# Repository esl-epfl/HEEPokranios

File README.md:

# HEEPokranios

HEEPokranios is a RISC-V SoC based on the open-source [X-HEEP](https://github.com/esl-epfl/x-heep) platform, designed to record intracranial EEG. Its 5 recording channels can be configured by the on-chip CPU and streamed out via DMA and different transmission options.

## SoC overview

- **MCU** — [X-HEEP](./hw/vendor/x-heep/): Ibex CPU, 2× DMA with dispatching mode, SPI (also used to load programs into SRAM wirelessly), JTAG, UART, 32 kB RAM, interrupts and timers.
- **Wireless power and data transfer** — [WPDT](./hw/vendor/analog-library/WPDT/): power from a 433 MHz inductive link, Manchester-encoded downlink (forwarded to the SPI) and uplink (serialized from a register), and a 1 MHz clock usable as system clock.
- **Power regulation** — [vREF](./hw/vendor/analog-library/vREF/), [iREF](./hw/vendor/analog-library/iREF/) and [iMIRROR](./hw/vendor/analog-library/iMIRROR/) generate the supplies and bias currents for the analog blocks from the WPDT rectifier output.
- **5× recording channels** — built as flavours of the [channel-multipath](./hw/ip/cheep_peripherals/peripherals/channel_multipath/) skeleton, combining acquisition blocks such as a low-noise amplifier ([LNA](./hw/vendor/analog-library/LNA/)), ΔΣ ADC ([DSM](./hw/vendor/analog-library/DSM/)), VCO-based ADC ([VCO](./hw/vendor/analog-library/VCO/)), level-crossing ADC ([LC](./hw/vendor/analog-library/LC/), [dLC](./hw/ip/cheep_peripherals/peripherals/dlc/)), band-power extraction ([BPE](./hw/vendor/analog-library/BPE/)) and an impedance-monitoring current DAC ([iDAC](./hw/vendor/analog-library/iDAC/)).

As a testing chip, most block inputs/outputs are exposed on pads, to be shorted at PCB level or at wire-bonding time.

## Getting started

1. Install the conda environment (Python tooling + fusesoc) and activate it:
   ```bash
   make conda
   conda activate heepokranios
   ```
   Make sure the following are also in your `PATH`: a RISC-V toolchain (supporting at least `rv32imc`), Verilator **4**, Verible and GTKWave. See _X-HEEP_'s [prerequisites](https://github.com/esl-epfl/x-heep#prerequisite) for details.

2. Generate the RTL and software from the SoC configuration (only needed once, and after any change to `config/cheep_configs.py` or a `.tpl` template):
   ```bash
   make mcu-gen
   ```

3. Build an application and run it on the Verilator simulation:
   ```bash
   make app PROJECT=hello_world
   make verilator-build
   make verilator-run
   ```
   The UART log is written to `build/sim-common/uart.log`, and waveforms can be inspected with `make verilator-waves`. `BOOT_MODE` defaults to `force` (firmware loaded directly into SRAM); `jtag` and `flash` boot are also supported.

`make help` lists all targets (use `make help WHICH=xheep` for the vendored _X-HEEP_ makefile).

## Documentation

- [_X-HEEP_ documentation](./hw/vendor/x-heep/docs/source/index.rst) — platform internals, configuration, programming and debugging.
- [HEEPokranios documentation](./docs/source/) — [analog front-end overview](./docs/source/Overview/Overview.md), [digital back-end](./docs/source/DBE/CIC_filter.md) and [LDO](./docs/source/FB/LDO.md) descriptions.
- [How to add new peripherals](./hw/ip/How%20to%20add%20new%20peripherals.md).
- [Analog library](./hw/vendor/analog-library/README.md) — structure and behavioral models of the analog blocks.

## License

HEEPokranios is distributed under the [Solderpad Hardware License v2.1](./LICENSE.md) (Apache-2.0 WITH SHL-2.1). The vendored [_X-HEEP_](./hw/vendor/x-heep/) and the analog library carry their own license terms.

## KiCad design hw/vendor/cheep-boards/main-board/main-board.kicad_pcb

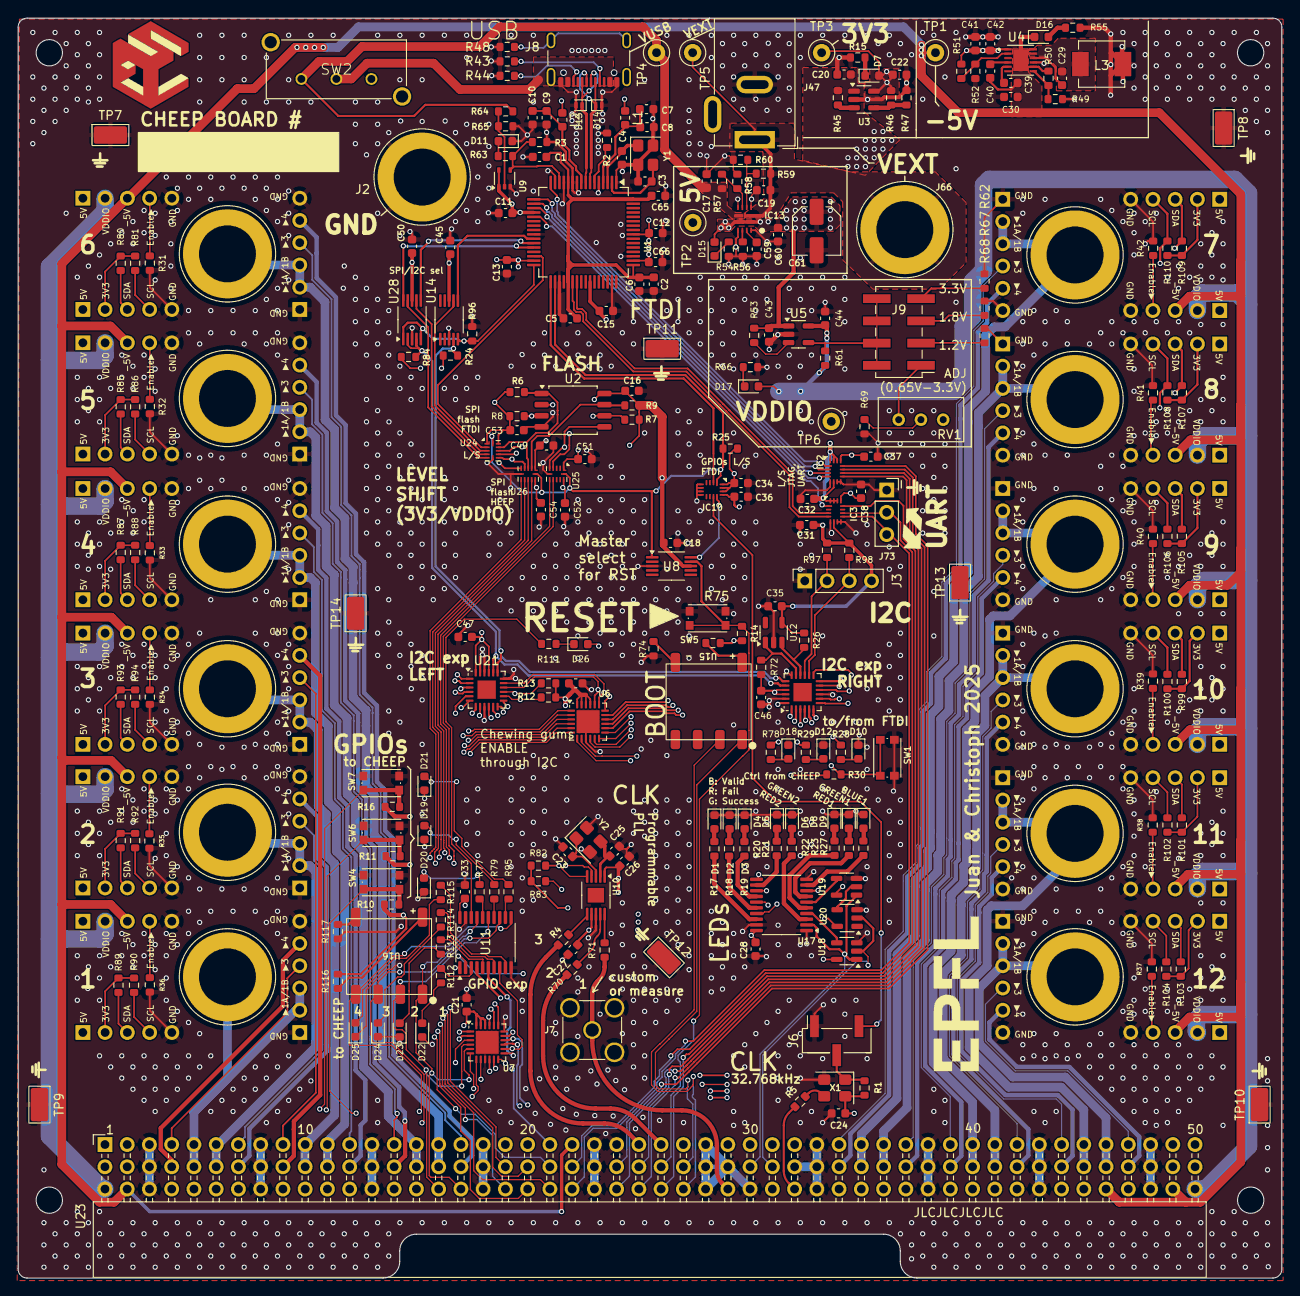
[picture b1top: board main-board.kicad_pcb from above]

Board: 4 copper layers, 144.3 x 143.8 mm, 277 parts (0 on the bottom side), 245 nets.

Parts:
C1, C2, C5, C7, C10, C11, C12, C13, C14, C15, C16, C18, C21, C24, C26, C27, C28, C29, C31, C32, C33, C34, C35, C36, C37, C38, C45, C46, C47, C49, C50, C51, C52, C53, C54, C59, C65, C66: 100nF; C_0603_1608Metric
C3, C4: 30pF; C_0603_1608Metric
C6: 3.3uF; C_0603_1608Metric
C8, C9, C41, C42: 4.7uF; C_0603_1608Metric
C17, C19, C60: 1uF; C_0603_1608Metric
C20, C43: 10uF; C_0603_1608Metric
C22, C30, C44: 22uF; C_0603_1608Metric
C23, C25: 1pF; C_0603_1608Metric
C39: 2.2uF; C_0603_1608Metric
C40: 5.6nF; C_0603_1608Metric
C61: 100uF; CP_Elec_5x4.5
CG1, CG2, CG3, CG4, CG5, CG6, CG7, CG8, CG9, CG10, CG11, CG12: chewing-gum
D1, D2, D3, D4, D5, D6, D7, D8, D9, D10, D11, D12, D15, D16, D17, D18, D19, D20, D21, D22, D23, D24, D25, D26: LED; LED_0603_1608Metric
D13, D14: PESD3V3U1UL; D_SOD-882
IC2, IC3, IC10: SN74AXC4T774RSVR; TI-UQFN-16
IC13: TPS2121RUXR; TI-VQFN-HR-12
J2, J66: Conn_01x01_Socket; Banana_Jack_1Pin
J3: Conn_01x04; PinSocket_1x04_P2.54mm_Vertical
J6: Conn_01x03; PinHeader_1x03_P2.54mm_Vertical_SMD_Pin1Right
J7: Conn_Boaxial; SMA_Amphenol_901-144_Vertical
J8: USB_C_Receptacle_USB2.0_16P; USB_C_Receptacle_GCT_USB4105-xx-A_16P_TopMnt_Horizontal
J9: Conn_02x04_Odd_Even; PinHeader_2x04_P2.54mm_Vertical_SMD
J47: Barrel Jack; BarrelJack_GCT_DCJ200-10-A_Horizontal
J73: Conn_01x03; PinSocket_1x03_P2.54mm_Vertical
L1, L2: 600nH; L_0603_1608Metric
L3: 10uH; L_Vishay_IHLP-2020
R1, R3, R12, R13, R24, R25, R26, R31, R32, R33, R34, R35, R36, R37, R38, R39, R40, R41, R42, R45, R53, R65, R72, R80, R81, R82, R83, R84, R85, R86, R87, R88, R89, R90, R91, R92, R93, R94, R96, R97, R98, R99, R100, R101, R102, R103, R104, R105, R106, R107, R108, R109, R110: 10k; R_0603_1608Metric
R2: 12k 1%; R_0603_1608Metric
R4, R5, R70, R71: 25; R_0603_1608Metric
R6, R7, R8, R9, R57, R59: 23.7k; R_0603_1608Metric
R10, R11, R14, R16, R30, R74, R75, R116, R117: 1k; R_0603_1608Metric
R15, R17, R18, R19, R20, R21, R22, R23, R27, R28, R29, R54, R55, R63, R66, R77, R78, R79, R95, R111, R112, R113, R114, R115: 5k; R_0603_1608Metric
R43, R44, R58, R60: 5.1k; R_0603_1608Metric
R46, R61: 100k; R_0603_1608Metric
R47, R62, R69: 20k; R_0603_1608Metric
R48: 51k; R_0603_1608Metric
R49: 226k; R_0603_1608Metric
R50: 49.9k; R_0603_1608Metric
R51: 3.32M; R_0603_1608Metric
R52: 1.33M; R_0603_1608Metric
R56: 59k; R_0603_1608Metric
R64: 4.7k; R_0603_1608Metric
R67: 44.2k; R_0603_1608Metric
R68: 86.6k; R_0603_1608Metric
RV1: 500k; Potentiometer_Bourns_3296W_Vertical
SW1, SW4, SW5, SW6, SW7: SW_Push; SW_Push_1P1T_NO_CK_KMR2
SW2: SW_DPST_x2; SW_TE_1825255-1
TP1, TP2, TP3, TP4, TP5, TP6: TestPoint_Loop_D1.80mm_Drill1.0mm_Beaded
TP7, TP8, TP9, TP10, TP11, TP12, TP13, TP14: 5029; TestPoint_Keystone_5019_Miniature
U1: FT4232HL; LQFP-64_10x10mm_P0.5mm
U2: W25Q128JVSIQ; SOIC-8_5.3x5.3mm_P1.27mm
U3, U5: TLV75801PDBV; SOT-23-5
U4: MAX17577; MAX17577-12-TDFN-EP
U6, U7: TCAL6416; WQFN-24-1EP_4x4mm_P0.5mm_EP2.6x2.6mm
U8, U14, U28: TS5A23159DGS; VSSOP-10_3x3mm_P0.5mm
U9: 74AHCT1G08; SOT-353_SC-70-5
U10: SI5351A-B-GTR; MSOP-10-1EP_3x3mm_P0.5mm_EP1.68x1.88mm
U11, U17: 74AHC244; TSSOP-20_4.4x6.5mm_P0.65mm
U12: 24AA02E-OT; SOT-23-5
U15, U16: BIWIN_DTS04GE_SMD
U18, U19: 74AHCT1G08; SOT-23-5
U20: 74AHC1G04; SOT-23-5
U21, U22: TCA9548ARGER; Texas_RGE0024C_VQFN-24-1EP_4x4mm_P0.5mm_EP2.1x2.1mm
U23: CHEEP_CONNECTOR_MAINBOARD
U24: TXBN0304RUT; Texas_R-PUQFN-N12
U25, U26: TXB0304RUT; Texas_R-PUQFN-N12
X1: OK322532.768KJBA4SL; Oscillator_SMD_SeikoEpson_SG8002CE-4Pin_3.2x2.5mm
Y1: Crystal_GND24; Crystal_SMD_3225-4Pin_3.2x2.5mm
Y2: NX3225GA-25.000M-STD-CRG-2; Crystal_SMD_3225-4Pin_3.2x2.5mm

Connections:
3V3: C11.1, C12.1, C13.1, C14.2, C15.1, C16.1, C18.1, C21.2, C22.1, C26.2, C28.2, C31.1, C32.1, C33.2, C34.1, C35.1, C45.1, C46.1, C47.1, C49.1, C50.1, C51.1, C53.1, C66.1, CG1.A2 (3V3), CG2.A2 (3V3), CG3.A2 (3V3), CG4.A2 (3V3), CG5.A2 (3V3), CG6.A2 (3V3), CG7.A2 (3V3), CG8.A2 (3V3), CG9.A2 (3V3), CG10.A2 (3V3), CG11.A2 (3V3), CG12.A2 (3V3), D7.2 (A), D26.2 (A), IC2.6 (DIR4), IC2.14 (VCCA), IC2.15 (DIR1), IC2.16 (DIR2), IC3.6 (DIR4), IC3.14 (VCCA), IC3.15 (DIR1), IC3.16 (DIR2), IC10.14 (VCCA), IC10.15 (DIR1), IC10.16 (DIR2), J3.4, L1.1, L2.1, R6.2, R7.2, R8.2, R9.2, R12.1, R13.1, R24.1, R25.1, R26.1, R30.2, R46.2, R72.1, R80.1, R81.1, R82.1, R83.1, R84.1, R85.1, R86.1, R87.1, R88.1, R89.1, R90.1, R91.1, R92.1, R93.1, R94.1, R97.1, R98.1, R99.1, R100.1, R101.1, R102.1, R103.1, R104.1, R105.1, R106.1, R107.1, R108.1, R109.1, R110.1, TP3.1, U1.20 (VCCIO), U1.31 (VCCIO), U1.42 (VCCIO), U1.50 (VREGIN), U1.56 (VCCIO), U2.8 (VCC), U3.5 (OUT), U6.18 (ADDR), U6.21 (VCCP), U6.22 (nINT), U6.23 (VCCI), U6.24 (nRST), U7.22 (nINT), U7.23 (VCCI), U7.24 (nRST), U8.8 (VCC), U9.1, U9.5 (VCC), U10.1 (VDD), U11.20 (VCC), U12.4 (V_{CC}), U14.8 (VCC), U17.20 (VCC), U18.5 (VCC), U19.5 (VCC), U20.5 (VCC), U21.21 (VCC), U21.24 (~RESET), U22.21 (VCC), U22.22 (A0), U22.24 (~RESET), U23.A2 (3V3), U23.A49 (3V3), U23.B2 (3V3), U23.B49 (3V3), U23.C44 (3V3), U24.1 (VCCA), U24.11 (VCCB), U25.1 (VCCA), U26.1 (VCCA), U28.8 (VCC)
5V: C20.1, C41.1, C42.1, C43.1, C60.1, C61.1, CG1.A1 (5V), CG1.B1 (5V), CG2.A1 (5V), CG2.B1 (5V), CG3.A1 (5V), CG3.B1 (5V), CG4.A1 (5V), CG4.B1 (5V), CG5.A1 (5V), CG5.B1 (5V), CG6.A1 (5V), CG6.B1 (5V), CG7.A1 (5V), CG7.B1 (5V), CG8.A1 (5V), CG8.B1 (5V), CG9.A1 (5V), CG9.B1 (5V), CG10.A1 (5V), CG10.B1 (5V), CG11.A1 (5V), CG11.B1 (5V), CG12.A1 (5V), CG12.B1 (5V), D15.2 (A), IC13.1 (VOUT_1), IC13.8 (VOUT_2), R45.2, R51.1, R53.2, TP2.1, U3.1 (IN), U4.1 (IN), U5.1 (IN), U23.A1 (5V), U23.A50 (5V), U23.B1 (5V), U23.B50 (5V), U23.C45 (5V)
-5V: C30.2, C39.2, C40.2, CG1.B3 (-5V), CG2.B3 (-5V), CG3.B3 (-5V), CG4.B3 (-5V), CG5.B3 (-5V), CG6.B3 (-5V), CG7.B3 (-5V), CG8.B3 (-5V), CG9.B3 (-5V), CG10.B3 (-5V), CG11.B3 (-5V), CG12.B3 (-5V), D16.1 (K), R50.2, TP1.1, U4.8 (SOUT), U4.12 (OUT), U4.13 (EP), U23.A22 (-5V), U23.C2 (-5V), U23.C46 (-5V), U23.C49 (-5V)
/BOOT_SEL: U15.1, U23.B27 (BOOT_SEL)
/BTN_FTDI: R30.1, SW1.1, U6.14
/CG_I2C_SCL_1: CG1.A4 (SCL), R90.2, U21.6 (SC2)
/CG_I2C_SCL_2: CG2.A4 (SCL), R92.2, U21.4 (SC1)
/CG_I2C_SCL_3: CG3.A4 (SCL), R94.2, U21.2 (SC0)
/CG_I2C_SCL_4: CG4.A4 (SCL), R88.2, U21.8 (SC3)
/CG_I2C_SCL_5: CG5.A4 (SCL), R86.2, U21.11 (SC4)
/CG_I2C_SCL_6: CG6.A4 (SCL), R81.2, U21.13 (SC5)
/CG_I2C_SCL_7: CG7.A4 (SCL), R110.2, U22.2 (SC0)
/CG_I2C_SCL_8: CG8.A4 (SCL), R108.2, U22.4 (SC1)
/CG_I2C_SCL_9: CG9.A4 (SCL), R106.2, U22.6 (SC2)
/CG_I2C_SCL_10: CG10.A4 (SCL), R100.2, U22.13 (SC5)
/CG_I2C_SCL_11: CG11.A4 (SCL), R102.2, U22.11 (SC4)
/CG_I2C_SCL_12: CG12.A4 (SCL), R104.2, U22.8 (SC3)
/CG_I2C_SDA_1: CG1.A3 (SDA), R89.2, U21.5 (SD2)
/CG_I2C_SDA_2: CG2.A3 (SDA), R91.2, U21.3 (SD1)
/CG_I2C_SDA_3: CG3.A3 (SDA), R93.2, U21.1 (SD0)
/CG_I2C_SDA_4: CG4.A3 (SDA), R87.2, U21.7 (SD3)
/CG_I2C_SDA_5: CG5.A3 (SDA), R85.2, U21.10 (SD4)
/CG_I2C_SDA_6: CG6.A3 (SDA), R80.2, U21.12 (SD5)
/CG_I2C_SDA_7: CG7.A3 (SDA), R109.2, U22.1 (SD0)
/CG_I2C_SDA_8: CG8.A3 (SDA), R107.2, U22.3 (SD1)
/CG_I2C_SDA_9: CG9.A3 (SDA), R105.2, U22.5 (SD2)
/CG_I2C_SDA_10: CG10.A3 (SDA), R99.2, U22.12 (SD5)
/CG_I2C_SDA_11: CG11.A3 (SDA), R101.2, U22.10 (SD4)
/CG_I2C_SDA_12: CG12.A3 (SDA), R103.2, U22.7 (SD3)
/CHEEP-CONNECTOR/CHEEP_I2C.SCL: R13.2, U21.15 (SC6), U23.C4 (I2C_SDA)
/CHEEP-CONNECTOR/CHEEP_I2C.SDA: R12.2, U21.14 (SD6), U23.C5 (I2C_SCL)
/CHEEP-CONNECTOR/JTAG.TCK: IC2.12 (B1), U23.B24 (JTAG_TCK)
/CHEEP-CONNECTOR/JTAG.TDI: IC2.11 (B2), U23.C25 (JTAG_TDI)
/CHEEP-CONNECTOR/JTAG.TDO: IC2.10 (B3), U23.C24 (JTAG_TDO)
/CHEEP-CONNECTOR/JTAG.TMS: IC2.9 (B4), U23.B25 (JTAG_TMS)
/CHEEP-CONNECTOR/JTAG.TRST: IC3.12 (B1), U23.C26 (JTAG_TRST)
/CHEEP-CONNECTOR/SPI_FLASH.CS0: U23.C19 (SPI_FLASH_SCK), U26.9 (B2)
/CHEEP-CONNECTOR/SPI_FLASH.SCK: U23.B19 (SPI_FLASH_CS), U25.8 (B3)
/CHEEP-CONNECTOR/SPI_FLASH.SD0: U23.B20 (SPI_FLASH_SD0), U25.7 (B4)
/CHEEP-CONNECTOR/SPI_FLASH.SD1: U23.C20 (SPI_FLASH_SD1), U26.8 (B3)
/CHEEP-CONNECTOR/SPI_FLASH.SD2: U23.B21 (SPI_FLASH_SD2), U26.7 (B4)
/CHEEP-CONNECTOR/SPI_FLASH.SD3: U23.C21 (SPI_FLASH_SD3), U26.10 (B1)
/CHEEP-CONNECTOR/UART.RX: IC3.10 (B3), J73.2, U23.B22 (UART_RX)
/CHEEP-CONNECTOR/UART.TX: IC3.9 (B4), J73.3, U23.C22 (UART_TX)
/CLK2: R70.1, U23.A26 (CLK2)
/CLK3: R4.1, U23.A25 (CLK3)
/CLK32K: R5.2, U23.C32 (CLK_32khz)
/CLOCK: J7.1 (In), R71.1, U23.C29 (CLK_FAST)
/CLOCK_SEL: IC10.11 (B2), J6.3
/EN_CG_1: CG1.B4 (ENABLE), R36.1, U6.6 (P05)
/EN_CG_2: CG2.B4 (ENABLE), R35.1, U6.5 (P04)
/EN_CG_3: CG3.B4 (ENABLE), R34.1, U6.4 (P03)
/EN_CG_4: CG4.B4 (ENABLE), R33.1, U6.3 (P02)
/EN_CG_5: CG5.B4 (ENABLE), R32.1, U6.2 (P01)
/EN_CG_6: CG6.B4 (ENABLE), R31.1, U6.1 (P00)
/EN_CG_7: CG7.B4 (ENABLE), R42.1, U6.13
/EN_CG_8: CG8.B4 (ENABLE), R41.1, U6.12
/EN_CG_9: CG9.B4 (ENABLE), R40.1, U6.11
/EN_CG_10: CG10.B4 (ENABLE), R39.1, U6.10
/EN_CG_11: CG11.B4 (ENABLE), R38.1, U6.8 (P07)
/EN_CG_12: CG12.B4 (ENABLE), R37.1, U6.7 (P06)
/EP_CLOCK_SEL: IC10.2 (A2), U1.33 (BDBUS6)
/EP_F_CS: U1.30 (BDBUS4), U24.2 (A1)
/EP_F_MISO: U24.5 (A4), U28.9
/EP_F_MOSI: U24.4 (A3), U28.7
/EP_F_SCK: U14.7, U24.3 (A2)
/EP_RX0: IC3.3 (A3), U1.39 (CDBUS1)
/EP_TCK: IC2.1 (A1), U1.16 (ADBUS0)
/EP_TDI: IC2.2 (A2), U1.17 (ADBUS1)
/EP_TDO: IC2.3 (A3), U1.18 (ADBUS2)
/EP_TMS: IC2.4 (A4), U1.19 (ADBUS3)
/EP_TRST: IC3.1 (A1), U1.21 (ADBUS4)
/EP_TX0: IC3.4 (A4), U1.38 (CDBUS0)
/EXEC_FLASH: U15.2, U23.C27 (EXEC_FLASH)
/EXIT_VALID: U17.2 (1A0), U18.1, U19.1, U23.B30 (EXIT_VALID)
/EXIT_VALUE: U18.2, U20.2, U23.B31 (EXIT_VALUE)
/GPIO_15: U7.3 (P02), U23.C9 (GPIO_15)
/GPIO_16: U7.2 (P01), U23.A32 (GPIO_16)
/GPIO_17: U7.1 (P00), U23.A31 (GPIO_17)
/GPIO_18: U7.15, U23.A30 (GPIO_18)
/GPIO_19: U7.16, U23.A29 (GPIO_19)
/GPIO_20: U7.17, U23.A21 (GPIO_20)
/GPIO_playground/GPIO.LED_B_1: U17.11 (2A3), U23.C39 (GPIO_3)
/GPIO_playground/GPIO.LED_G_1: U7.6 (P05), U17.13 (2A2), U23.C34 (GPIO_7)
/GPIO_playground/GPIO.LED_G_2: U7.8 (P07), U17.17 (2A0), U23.C36 (GPIO_5)
/GPIO_playground/GPIO.LED_R_1: U7.7 (P06), U17.15 (2A1), U23.C35 (GPIO_6)
/GPIO_playground/GPIO.LED_R_2: U17.8 (1A3), U23.C37 (GPIO_4)
/GPIO_playground/GPIO.PB_1: R10.1, SW4.1, U7.12, U11.4 (1A1), U23.C12 (GPIO_12)
/GPIO_playground/GPIO.PB_2: R11.1, SW6.1, U7.13, U11.6 (1A2), U23.C11 (GPIO_13)
/GPIO_playground/GPIO.PB_3: R16.1, SW7.1, U7.14, U11.8 (1A3), U23.C10 (GPIO_14)
/GPIO_playground/GPIO.SW_1: U7.5 (P04), U11.17 (2A0), U16.1, U23.C17 (GPIO_8)
/GPIO_playground/GPIO.SW_2: U7.4 (P03), U11.15 (2A1), U16.2, U23.C16 (GPIO_9)
/GPIO_playground/GPIO.SW_3: U7.10, U11.13 (2A2), U16.3, U23.C15 (GPIO_10)
/GPIO_playground/GPIO.SW_4: U7.11, U11.11 (2A3), U16.4, U23.C14 (GPIO_11)
/I2C_expander/SCL_EEPROM: R72.2, U12.1 (SCL), U22.17 (SC7)
/I2C_expander/SCL_EXT: J3.2, R97.2, U22.15 (SC6)
/I2C_expander/SDA_EEPROM: R26.2, U12.3 (SDA), U22.16 (SD7)
/I2C_expander/SDA_EXT: J3.3, R98.2, U22.14 (SD6)
/LED_FTDI_1: R28.1, U6.17
/LED_FTDI_2: R29.1, U6.16
/LED_FTDI_3: R78.1, U6.15
/LX: C29.2, L3.1, U4.11 (LX)
/LevelTransMeasCurrent/FLASH_CS: R6.1, U2.1 (~CS), U24.10 (B1), U26.3 (A2)
/LevelTransMeasCurrent/FLASH_MISO: U2.2 (DO/IO1), U24.7 (B4), U26.4 (A3)
/LevelTransMeasCurrent/FLASH_MOSI: U2.5 (DI/IO0), U24.8 (B3), U25.5 (A4)
/LevelTransMeasCurrent/FLASH_SCK: R7.1, U2.6 (CLK), U24.9 (B2), U25.4 (A3)
/LevelTransMeasCurrent/FLASH_nHLD_nRST: R9.1, U2.7 (~HLD/~RST/IO3), U26.2 (A1)
/LevelTransMeasCurrent/FLASH_nWP: R8.1, U2.3 (~WP/IO2), U26.5 (A4)
/Programmer/FLASH_MISO_SDA: U1.28 (BDBUS2), U28.10
/Programmer/FLASH_MOSI_SDA: U1.27 (BDBUS1), U28.6
/Programmer/FLASH_SCK_SCL: U1.26 (BDBUS0), U14.6
/Programmer/FTDI_ACTIVE: R3.1, R63.2, U1.14 (~RESET), U9.4
/Programmer/SPI_I2C_SEL: R96.1, U1.32 (BDBUS5), U14.5, U28.1, U28.5
/Programmer/VCORE: C1.1, C2.1, C5.1, C6.1, C65.1, U1.12 (VCORE), U1.37 (VCORE), U1.49 (VREGOUT), U1.64 (VCORE)
/USB_D+: D13.1 (K), J8.A6 (D+), J8.B6 (D+), U1.8 (DP)
/USB_D-: D14.1 (K), J8.A7 (D-), J8.B7 (D-), U1.7 (DM)
/VBUS: J8.A4 (VBUS), J8.A9 (VBUS), J8.B4 (VBUS), J8.B9 (VBUS), SW2.2 (B)
/VEXT: C19.2, IC13.2 (VIN2), J47.1, J66.1, R59.1, TP5.1
/VUSB: C17.1, IC13.7 (VIN1), R57.2, R64.1, SW2.1 (A), TP4.1
/Vout_A_1: CG1.C2 (OUT_1), CG1.C3 (OUT_2), CG1.D1 (OUT_0), U23.A5 (VOUT.A1.1), U23.B5 (VOUT.A1.1)
/Vout_A_2: CG2.C2 (OUT_1), CG2.C3 (OUT_2), CG2.D1 (OUT_0), U23.A6 (VOUT.A2.1), U23.B6 (VOUT.A2.1)
/Vout_A_3: CG3.C2 (OUT_1), CG3.C3 (OUT_2), CG3.D1 (OUT_0), U23.A10 (VOUT.A3.1), U23.B10 (VOUT.A3.1)
/Vout_A_4: CG4.C2 (OUT_1), CG4.C3 (OUT_2), CG4.D1 (OUT_0), U23.A11 (VOUT.A4.1), U23.B11 (VOUT.A4.1)
/Vout_A_5: CG5.C2 (OUT_1), CG5.C3 (OUT_2), CG5.D1 (OUT_0), U23.A15 (VOUT.A5.1), U23.B15 (VOUT.A5.1)
/Vout_A_6: CG6.C2 (OUT_1), CG6.C3 (OUT_2), CG6.D1 (OUT_0), U23.A16 (VOUT.A6.1), U23.B16 (VOUT.A6.1)
/Vout_A_7: CG7.C2 (OUT_1), CG7.C3 (OUT_2), CG7.D1 (OUT_0), U23.A35 (VOUT.A7.1), U23.B35 (VOUT.A7.1)
/Vout_A_8: CG8.C2 (OUT_1), CG8.C3 (OUT_2), CG8.D1 (OUT_0), U23.A36 (VOUT.A8.1), U23.B36 (VOUT.A8.1)
/Vout_A_9: CG9.C2 (OUT_1), CG9.C3 (OUT_2), CG9.D1 (OUT_0), U23.A40 (VOUT.A9.1), U23.B40 (VOUT.A9.1)
/Vout_A_10: CG10.C2 (OUT_1), CG10.C3 (OUT_2), CG10.D1 (OUT_0), U23.A41 (VOUT.A10.1), U23.B41 (VOUT.A10.1)
/Vout_A_11: CG11.C2 (OUT_1), CG11.C3 (OUT_2), CG11.D1 (OUT_0), U23.A45 (VOUT.A11.1), U23.B45 (VOUT.A11.1)
/Vout_A_12: CG12.C2 (OUT_1), CG12.C3 (OUT_2), CG12.D1 (OUT_0), U23.A46 (VOUT.A12.1), U23.B46 (VOUT.A12.1)
/Vout_B_1: CG1.C5 (OUT_4), U23.B4 (VOUT.B1.1)
/Vout_B_2: CG2.C5 (OUT_4), U23.B7 (VOUT.B2.1)
/Vout_B_3: CG3.C5 (OUT_4), U23.B9 (VOUT.B3.1)
/Vout_B_4: CG4.C5 (OUT_4), U23.B12 (VOUT.B4.1)
/Vout_B_5: CG5.C5 (OUT_4), U23.B14 (VOUT.B5.1)
/Vout_B_6: CG6.C5 (OUT_4), U23.B17 (VOUT.B6.1)
/Vout_B_7: CG7.C5 (OUT_4), U23.B34 (VOUT.B7.1)
/Vout_B_8: CG8.C5 (OUT_4), U23.B37 (VOUT.B8.1)
/Vout_B_9: CG9.C5 (OUT_4), U23.B39 (VOUT.B9.1)
/Vout_B_10: CG10.C5 (OUT_4), U23.B42 (VOUT.B10.1)
/Vout_B_11: CG11.C5 (OUT_4), U23.B44 (VOUT.B11.1)
/Vout_B_12: CG12.C5 (OUT_4), U23.B47 (VOUT.B12.1)
/Vout_diff_1: CG1.C4 (OUT_3), U23.A4 (VOUT.B1.diff)
/Vout_diff_2: CG2.C4 (OUT_3), U23.A7 (VOUT.B2.diff)
/Vout_diff_3: CG3.C4 (OUT_3), U23.A9 (VOUT.B3.diff)
/Vout_diff_4: CG4.C4 (OUT_3), U23.A12 (VOUT.B4.diff)
/Vout_diff_5: CG5.C4 (OUT_3), U23.A14 (VOUT.B5.diff)
/Vout_diff_6: CG6.C4 (OUT_3), U23.A17 (VOUT.B6.diff)
/Vout_diff_7: CG7.C4 (OUT_3), U23.A34 (VOUT.B7.diff)
/Vout_diff_8: CG8.C4 (OUT_3), U23.A37 (VOUT.B8.diff)
/Vout_diff_9: CG9.C4 (OUT_3), U23.A39 (VOUT.B9.diff)
/Vout_diff_10: CG10.C4 (OUT_3), U23.A42 (VOUT.B10.diff)
/Vout_diff_11: CG11.C4 (OUT_3), U23.A44 (VOUT.B11.diff)
/Vout_diff_12: CG12.C4 (OUT_3), U23.A47 (VOUT.B12.diff)
/nRST: R14.1, SW5.1, U8.9, U11.2 (1A0), U23.B26 (nRST)
/nRST_HEEP_FTDI: IC10.1 (A1), R25.2, U1.34 (BDBUS7), U8.1, U24.12 (~OE), U25.12 (OE), U26.12 (OE)
GND: C1.2, C2.2, C3.1, C4.1, C5.2, C6.2, C7.2, C8.2, C9.2, C10.2, C11.2, C12.2, C13.2, C14.1, C15.2, C16.2, C17.2, C18.2, C19.1, C20.2, C21.1, C22.2, C23.2, C24.2, C25.2, C26.1, C27.2, C28.1, C30.1, C31.2, C32.2, C33.1, C34.2, C35.2, C36.2, C37.2, C38.2, C41.2, C42.2, C43.2, C44.2, C45.2, C46.2, C47.2, C49.2, C50.2, C51.2, C52.2, C53.2, C54.2, C59.2, C60.2, C61.2, C65.2, C66.2, CG1.A5 (GND), CG1.B5 (GND), CG1.C1 (GND), CG1.C6 (GND), CG2.A5 (GND), CG2.B5 (GND), CG2.C1 (GND), CG2.C6 (GND), CG3.A5 (GND), CG3.B5 (GND), CG3.C1 (GND), CG3.C6 (GND), CG4.A5 (GND), CG4.B5 (GND), CG4.C1 (GND), CG4.C6 (GND), CG5.A5 (GND), CG5.B5 (GND), CG5.C1 (GND), CG5.C6 (GND), CG6.A5 (GND), CG6.B5 (GND), CG6.C1 (GND), CG6.C6 (GND), CG7.A5 (GND), CG7.B5 (GND), CG7.C1 (GND), CG7.C6 (GND), CG8.A5 (GND), CG8.B5 (GND), CG8.C1 (GND), CG8.C6 (GND), CG9.A5 (GND), CG9.B5 (GND), CG9.C1 (GND), CG9.C6 (GND), CG10.A5 (GND), CG10.B5 (GND), CG10.C1 (GND), CG10.C6 (GND), CG11.A5 (GND), CG11.B5 (GND), CG11.C1 (GND), CG11.C6 (GND), CG12.A5 (GND), CG12.B5 (GND), CG12.C1 (GND), CG12.C6 (GND), D1.1 (K), D2.1 (K), D3.1 (K), D4.1 (K), D5.1 (K), D6.1 (K), D8.1 (K), D9.1 (K), D10.1 (K), D11.1 (K), D12.1 (K), D13.2 (A), D14.2 (A), D18.1 (K), D19.1 (K), D20.1 (K), D21.1 (K), D22.1 (K), D23.1 (K), D24.1 (K), D25.1 (K), IC2.5 (DIR3), IC2.7 (~OE), IC2.8 (GND), IC3.5 (DIR3), IC3.7 (~OE), IC3.8 (GND), IC10.5 (DIR3), IC10.6 (DIR4), IC10.7 (~OE), IC10.8 (GND), IC13.3 (CP2), IC13.6 (PR1), IC13.9 (ST), IC13.12 (GND), J2.1, J3.1, J6.1, J7.2 (Ext), J8.A1 (GND), J8.A12 (GND), J8.B1 (GND), J8.B12 (GND), J47.2, J73.1, L3.2, R2.1, R3.2, R15.2, R31.2, R32.2, R33.2, R34.2, R35.2, R36.2, R37.2, R38.2, R39.2, R40.2, R41.2, R42.2, R43.2, R44.2, R47.2, R48.2, R49.1, R52.2, R54.2, R55.2, R56.2, R58.1, R60.1, R62.2, R65.2, R66.2, R67.2, R68.2, R69.2, R74.2, R96.2, R117.1, SW1.2, SW4.2, SW5.2, SW6.2, SW7.2, TP7.1, TP8.1, TP9.1, TP10.1, TP11.1, TP12.1, TP13.1, TP14.1, U1.1 (GND), U1.5 (GND), U1.10 (AGND), U1.11 (GND), U1.13 (TEST), U1.15 (GND), U1.25 (GND), U1.35 (GND), U1.47 (GND), U1.51 (GND), U2.4 (GND), U3.2 (GND), U4.9 (GND), U5.2 (GND), U6.9 (GND), U6.25 (GND), U7.9 (GND), U7.18 (ADDR), U7.25 (GND), U8.3 (GND), U9.3 (GND), U10.8 (GND), U11.1 (1OE), U11.10 (GND), U11.19 (2OE), U12.2 (V_{SS}), U14.3 (GND), U17.1 (1OE), U17.10 (GND), U17.19 (2OE), U18.3 (GND), U19.3 (GND), U20.3 (GND), U21.9 (GND), U21.18 (A2), U21.22 (A0), U21.23 (A1), U22.9 (GND), U22.18 (A2), U22.23 (A1), U23.A3 (GND), U23.A8 (GND), U23.A13 (GND), U23.A18 (GND), U23.A23 (GND), U23.A24 (GND), U23.A28 (GND), U23.A33 (GND), U23.A38 (GND), U23.A43 (GND), U23.A48 (GND), U23.B3 (GND), U23.B8 (GND), U23.B13 (GND), U23.B18 (GND), U23.B23 (GND), U23.B28 (GND), U23.B29 (GND), U23.B32 (GND), U23.B33 (GND), U23.B38 (GND), U23.B43 (GND), U23.B48 (GND), U23.C3 (GND), U23.C8 (GND), U23.C13 (GND), U23.C18 (GND), U23.C23 (GND), U23.C28 (GND), U23.C30 (GND), U23.C33 (GND), U23.C38 (GND), U23.C43 (GND), U23.C48 (GND), U24.6 (GND), U25.6 (GND), U26.6 (GND), U28.3 (GND), X1.2 (GND), Y1.2, Y1.4, Y2.2, Y2.4
unnamed: D1.2 (A), R17.2
unnamed: D2.2 (A), R18.2
unnamed: D3.2 (A), R19.2
unnamed: D4.2 (A), R20.2
unnamed: D5.2 (A), R21.2
unnamed: D6.2 (A), R22.2
unnamed: D7.1 (K), R15.1
unnamed: D8.2 (A), R23.2
unnamed: D9.2 (A), R27.2
unnamed: D10.2 (A), R28.2
unnamed: D11.2 (A), R63.1
unnamed: D12.2 (A), R29.2
unnamed: D15.1 (K), R54.1
unnamed: D16.2 (A), R55.1
unnamed: D17.1 (K), R66.1
unnamed: D18.2 (A), R78.2
unnamed: D19.2 (A), R79.2
unnamed: D20.2 (A), R77.2
unnamed: D21.2 (A), R95.2
unnamed: D22.2 (A), R112.2
unnamed: D23.2 (A), R113.2
unnamed: D24.2 (A), R114.2
unnamed: D25.2 (A), R115.2
unnamed: D26.1 (K), R111.2
unnamed: IC10.12 (B1), U8.10
unnamed: IC13.10 (ILIM), R56.1
unnamed: IC13.5 (OV1), R57.1, R58.2
unnamed: IC13.4 (OV2), R59.2, R60.2
unnamed: C59.1, IC13.11 (SS)
unnamed: J6.2, R1.2, X1.1 (TRI)
unnamed: J8.A5 (CC1), R43.1
unnamed: J8.B5 (CC2), R44.1
unnamed: J8.S1 (SHIELD), R48.1
unnamed: J9.1, RV1.1
unnamed: J9.2, J9.4, J9.6, J9.8, R61.1, U5.4 (FB)
unnamed: J9.3, R68.1
unnamed: J9.5, R67.1
unnamed: J9.7, R62.1
unnamed: R64.2, R65.1, U9.2
unnamed: R69.1, RV1.2
unnamed: C3.2, U1.2 (OSCI), Y1.3
unnamed: C4.2, U1.3 (OSCO), Y1.1
unnamed: R2.2, U1.6 (REF)
unnamed: C7.1, C8.1, L1.2, U1.4 (VPHY)
unnamed: C9.1, C10.1, L2.2, U1.9 (VPLL)
unnamed: R45.1, U3.3 (EN)
unnamed: R46.1, R47.1, U3.4 (FB)
unnamed: C29.1, U4.10 (BST)
unnamed: R51.2, R52.1, U4.2 (EN/UVLO)
unnamed: R49.2, R50.1, U4.7 (FB)
unnamed: C40.1, U4.4 (SS)
unnamed: C39.1, U4.5 (VCC)
unnamed: R53.1, U5.3 (EN)
unnamed: R71.2, U10.10 (CLK0)
unnamed: R70.2, U10.9 (CLK1)
unnamed: R4.2, U10.6 (CLK2)
unnamed: C25.1, U10.2 (XA), Y2.3
unnamed: C23.1, U10.3 (XB), Y2.1
unnamed: R111.1, U11.18 (1Y0)
unnamed: R77.1, U11.16 (1Y1)
unnamed: R79.1, U11.14 (1Y2)
unnamed: R95.1, U11.12 (1Y3)
unnamed: R112.1, U11.3 (2Y0)
unnamed: R113.1, U11.5 (2Y1)
unnamed: R114.1, U11.7 (2Y2)
unnamed: R115.1, U11.9 (2Y3)
unnamed: R75.1, U15.5 (+)
unnamed: R74.1, U15.6 (-)
unnamed: R116.2, U16.5 (+)
unnamed: R117.2, U16.6 (-)
unnamed: U17.4 (1A1), U18.4
unnamed: U17.6 (1A2), U19.4
unnamed: R17.1, U17.18 (1Y0)
unnamed: R18.1, U17.16 (1Y1)
unnamed: R19.1, U17.14 (1Y2)
unnamed: R20.1, U17.12 (1Y3)
unnamed: R21.1, U17.3 (2Y0)
unnamed: R22.1, U17.5 (2Y1)
unnamed: R23.1, U17.7 (2Y2)
unnamed: R27.1, U17.9 (2Y3)
unnamed: U19.2, U20.4
unnamed: R5.1, X1.3 (OUT)
SCL: R24.2, U14.4, U21.19 (SCL), U22.19 (SCL)
SCL_LEFT: R83.2, U6.19 (SCL), U7.19 (SCL), U10.4 (SCL), U21.17 (SC7)
SDA: R84.2, U21.20 (SDA), U22.20 (SDA), U28.2, U28.4
SDA_LEFT: R82.2, U6.20 (SDA), U7.20 (SDA), U10.5 (SDA), U21.16 (SD7)
VDDIO: C24.1, C27.1, C36.1, C37.1, C38.1, C44.1, C52.1, C54.1, CG1.B2 (3V3), CG2.B2 (3V3), CG3.B2 (3V3), CG4.B2 (3V3), CG5.B2 (3V3), CG6.B2 (3V3), CG7.B2 (3V3), CG8.B2 (3V3), CG9.B2 (3V3), CG10.B2 (3V3), CG11.B2 (3V3), CG12.B2 (3V3), D17.2 (A), IC2.13 (VCCB), IC3.13 (VCCB), IC10.13 (VCCB), R1.1, R10.2, R11.2, R14.2, R16.2, R61.2, R75.2, R116.1, TP6.1, U5.5 (OUT), U7.21 (VCCP), U10.7 (VDDO), U23.A27 (VDDIO), U23.C1 (VDDIO), U23.C31 (VDDIO), U23.C50 (VDDIO), U25.11 (VCCB), U26.11 (VCCB), X1.4 (Vcc)
